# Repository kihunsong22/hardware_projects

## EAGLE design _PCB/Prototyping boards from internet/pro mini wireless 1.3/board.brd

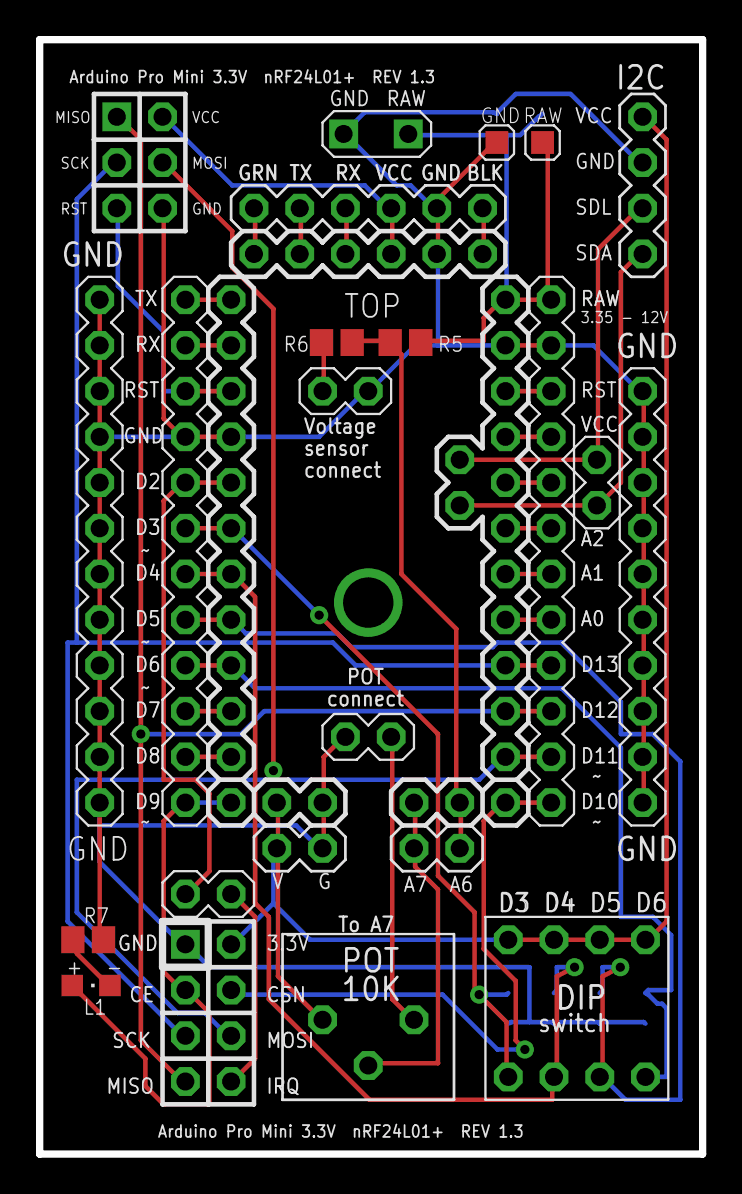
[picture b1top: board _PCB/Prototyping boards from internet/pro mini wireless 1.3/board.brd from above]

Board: 2 copper layers, 36.8 x 61.9 mm, 23 parts (0 on the bottom side), 37 nets.

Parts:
U$1: ARDUINO_PRO_MINI_3.3V
U$2, U$3: 12_PIN_HEADER
U$4: PAD_CONNECT
U$5: 6_PIN_HEADER
U$6: 2_SPACE_2_HEADER
U$7: 18650_HOLDER_FITTED
U$8: 12_PIN_HEADER
U$9: 4-DIP
U$10, U$14, U$15, U$20: 2_PIN_HEADER
U$11: 4_PIN_HEADER
U$12: 10_PIN_HEADER
U$13: POT_10K
U$16, U$17: 1k; 0805_SMD_RESISTOR
U$18: 0805_SMD_LED
U$19: ???R; 0805_SMD_RESISTOR
U$21: NRF24L01; NRFL2401
U$22: SCREWTERMINAL
U$23: SPI

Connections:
BLK: U$1.BLK, U$5.6
GND: U$1.G, U$1.GND_0, U$1.GND_1, U$1.GND_2, U$2.4, U$3.2, U$4.GND_1, U$4.GND_2, U$5.5, U$6.2, U$8.1, U$8.2, U$8.3, U$8.4, U$8.5, U$8.6, U$8.7, U$8.8, U$8.9, U$8.10, U$8.11, U$8.12, U$9.GND_1, U$9.GND_2, U$9.GND_3, U$9.GND_4, U$11.2, U$12.P$1, U$12.P$2, U$12.P$3, U$12.P$4, U$12.P$5, U$12.P$6, U$12.P$7, U$12.P$8, U$12.P$9, U$12.P$10, U$14.2, U$15.1, U$19.2, U$21.GND, U$22.GND, U$23.GND
GRN: U$1.GRN, U$5.1
unnamed: U$1.TX/D0, U$2.1
unnamed: U$1.RX/D1, U$2.2
unnamed: U$1.RST_1, U$2.3, U$23.RESET
unnamed: U$1.RX, U$5.3
unnamed: U$10.1, U$21.IRQ
unnamed: U$1.VCC_0, U$3.4
unnamed: U$1.A5, U$11.3, U$20.1
unnamed: U$1.VCC_1, U$5.4, U$23.VCC
unnamed: U$15.2, U$16.1
unnamed: U$13.CCW, U$14.1
unnamed: U$18.C, U$19.1
unnamed: U$1.D10, U$3.12, U$21.CSN
unnamed: U$1.D11, U$3.11, U$21.MOSI, U$23.MOSI
unnamed: U$1.D3, U$2.6, U$9.D3, U$9.OFF_1
unnamed: U$1.RST_0, U$3.3
unnamed: U$1.A3, U$3.5
unnamed: U$1.A2, U$3.6
unnamed: U$1.A1, U$3.7
unnamed: U$1.A0, U$3.8
unnamed: U$1.A4, U$11.4, U$20.2
unnamed: U$1.A6, U$6.4, U$16.2, U$17.1
unnamed: U$1.D9, U$2.12, U$18.A, U$21.CE
unnamed: U$1.D2, U$2.5, U$10.2
unnamed: U$1.A7, U$6.3, U$13.WIPER
unnamed: U$1.RAW, U$3.1, U$4.RAW_1, U$4.RAW_2, U$17.2, U$22.RAW_3
unnamed: U$1.D12, U$3.10, U$21.MISO, U$23.MISO
unnamed: U$1.D5, U$2.8, U$9.D5, U$9.OFF_3
unnamed: U$1.D4, U$2.7, U$9.D4, U$9.OFF_2
unnamed: U$1.D7, U$2.10
unnamed: U$1.D8, U$2.11
unnamed: U$1.D6, U$2.9, U$9.D6, U$9.OFF_4
unnamed: U$1.D13, U$3.9, U$21.SCK, U$23.SCK
TX: U$1.TX, U$5.2
VCC: U$1.V, U$6.1, U$9.VCC_1, U$9.VCC_2, U$9.VCC_3, U$9.VCC_4, U$11.1, U$13.CW, U$21.3.3V

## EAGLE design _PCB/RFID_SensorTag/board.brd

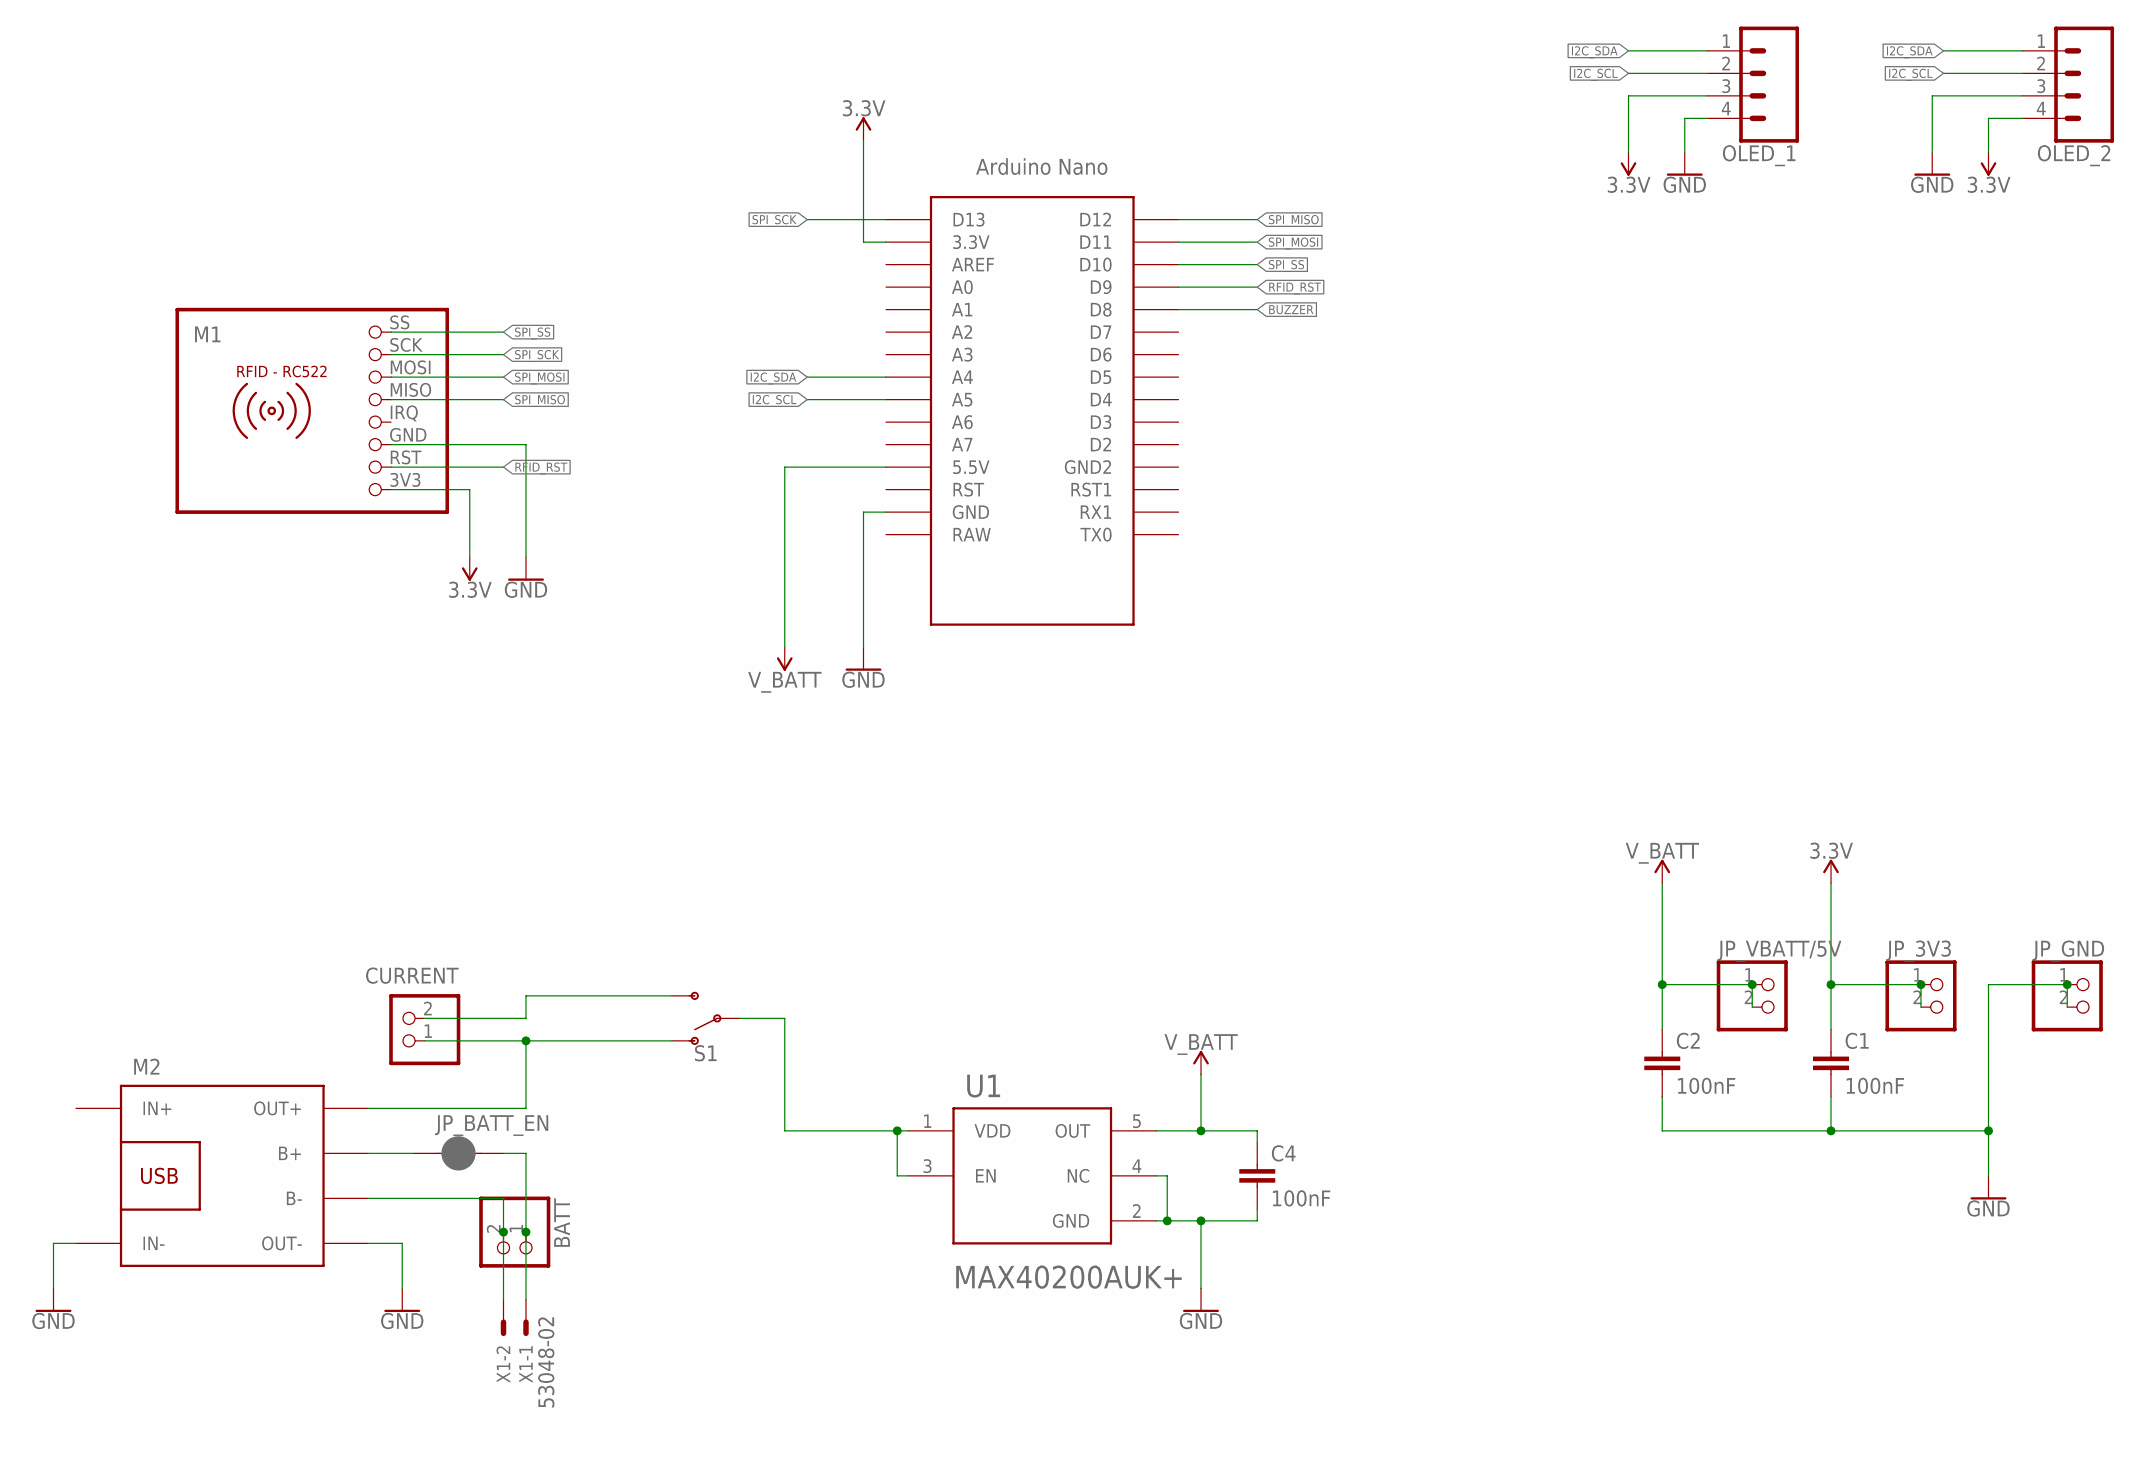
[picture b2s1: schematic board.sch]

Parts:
BATT: PINHD-1X2; 1X02
C1, C2, C4: 100nF; C0805
CURRENT: PINHD-1X2; 1X02
JP_3V3: PINHD-1X2; 1X02
JP_BATT_EN: JUMPER-SMT_2_NC_PASTE_SILK; SMT-JUMPER_2_NC_PASTE_SILK
JP_GND: PINHD-1X2; 1X02
JP_VBATT/5V: PINHD-1X2; 1X02
M1: RFID-RC522
M2: BATTERY-CHARGER-LI-PROT
OLED_1, OLED_2: CONN_04; 1X04
S1: SWITCH-SPDT-PTH-11.6X4.0MM; SWITCH_SPDT_PTH_11.6X4.0MM
U1: MAXIM_ELECTRONICS_MAX40200AUK+MAXIM_ELECTRONICS_M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; MAXIM_ELECTRONICS_MAX40200AUK+_0
U$1: NANO_ICSP-REMOVED
X1: 53048-02

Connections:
3.3V: C1.1, JP_3V3.1, JP_3V3.2, M1.3V3 (1), OLED_1.3, OLED_2.4, U$1.3.3V
BATT_VOUT: S1.2, U1.1 (VDD), U1.3 (EN)
BUZZER: U$1.D8
GND: C1.2, C2.2, C4.2, JP_GND.1, JP_GND.2, M1.GND (3), M2.IN-, M2.OUT-, OLED_1.4, OLED_2.3, U1.2 (GND), U1.4 (NC), U$1.GND
I2C_SCL: OLED_1.2, OLED_2.2, U$1.A5
I2C_SDA: OLED_1.1, OLED_2.1, U$1.A4
unnamed: CURRENT.1, M2.OUT+, S1.1 (O)
unnamed: BATT.1, JP_BATT_EN.2, X1.1
unnamed: CURRENT.2, S1.3 (S)
unnamed: BATT.2, M2.B-, X1.2
unnamed: JP_BATT_EN.1, M2.B+
RFID_RST: M1.RST (2), U$1.D9
SPI_MISO: M1.MISO (5), U$1.D12
SPI_MOSI: M1.MOSI (6), U$1.D11
SPI_SCK: M1.SCK (7), U$1.D13
SPI_SS: M1.SS (8), U$1.D10
V_BATT: C2.1, C4.1, JP_VBATT/5V.1, JP_VBATT/5V.2, U1.5 (OUT), U$1.5V (5.5V)

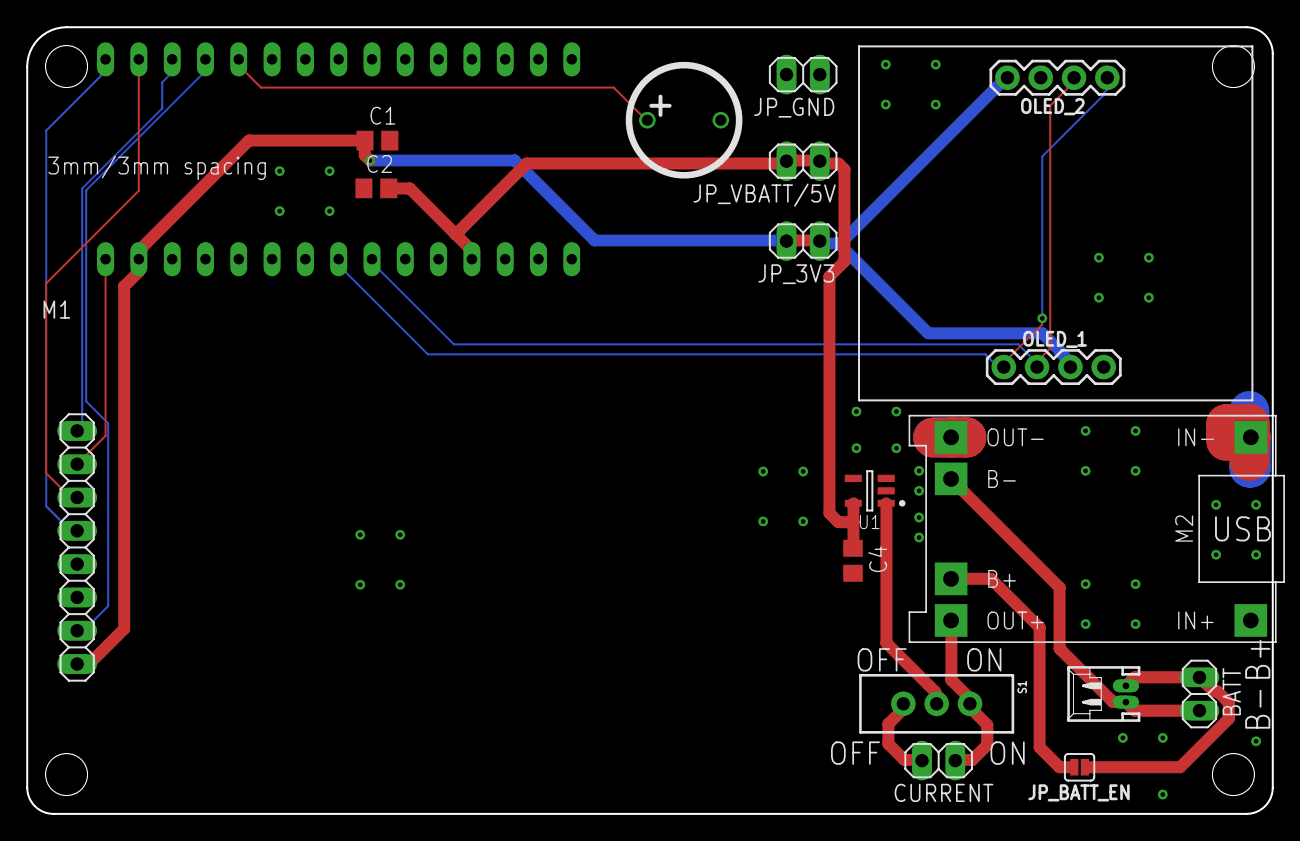
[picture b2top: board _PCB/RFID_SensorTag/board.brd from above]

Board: 2 copper layers, 95.0 x 60.0 mm, 17 parts (0 on the bottom side), 16 nets.

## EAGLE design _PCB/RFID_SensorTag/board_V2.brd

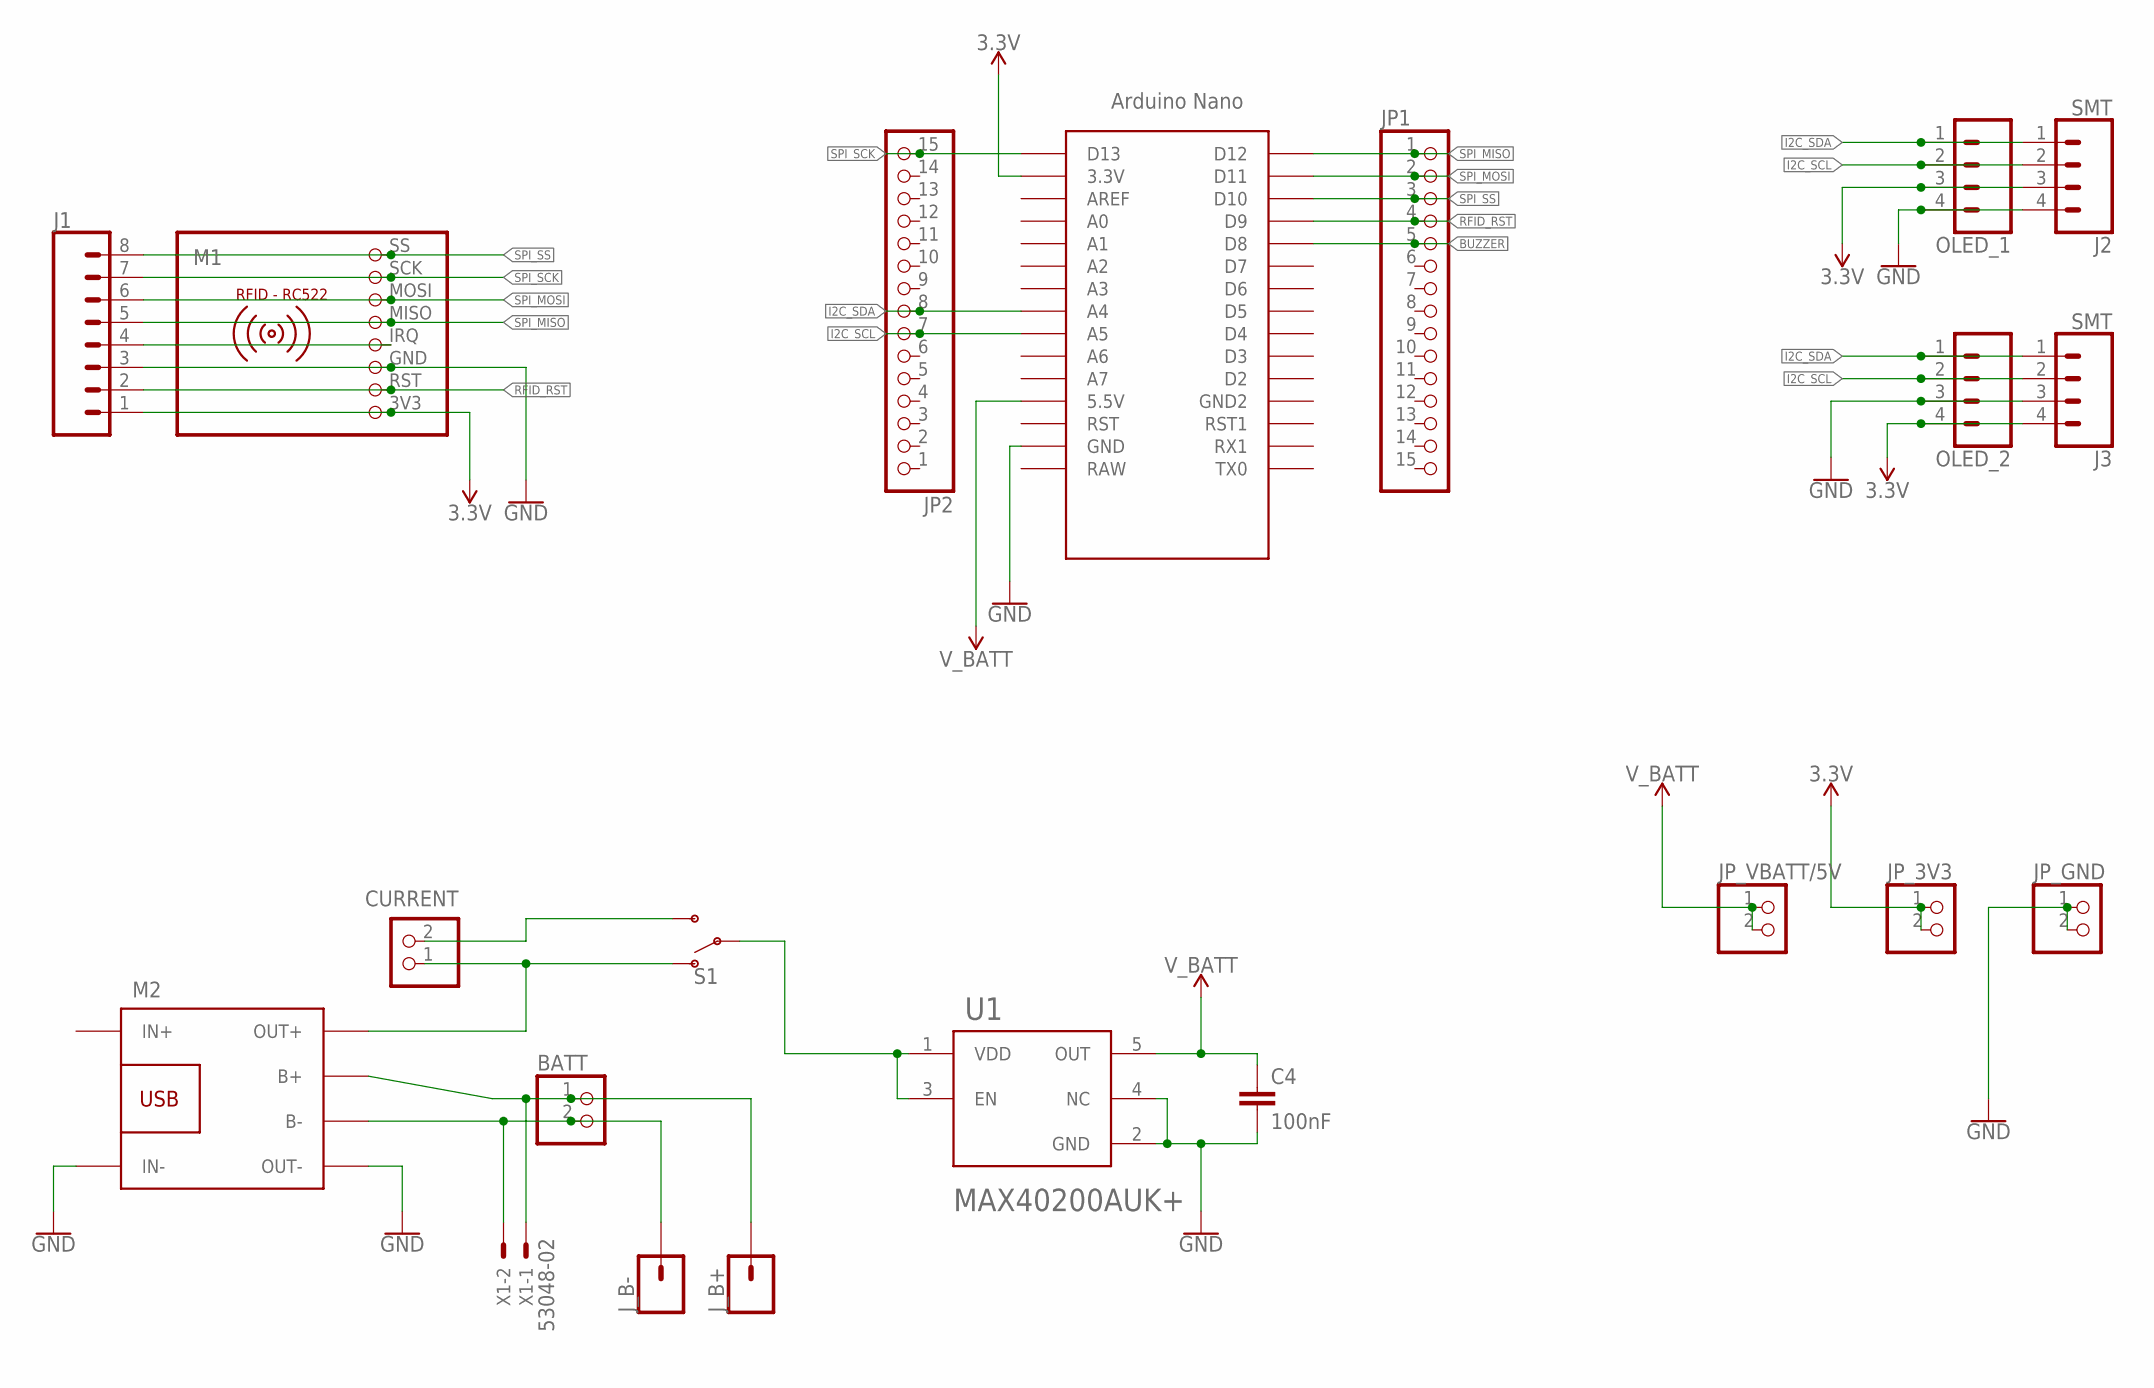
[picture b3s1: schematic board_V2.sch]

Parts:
BATT: PINHD-1X2; 1X02
C4: 100nF; C0805
CURRENT: PINHD-1X2; 1X02
J1: CONN_08SMD-COMBO-FEMALE; 1X08_SMD_COMBINED
J2, J3: SMT; 1X04_SMD_VERTICAL_COMBO
JP1, JP2: PINHD-1X151X15_SMT; 1X15_SMT
JP_3V3: PINHD-1X2; 1X02
JP_GND: PINHD-1X2; 1X02
JP_VBATT/5V: PINHD-1X2; 1X02
J_B+: CONN_01OFFSET; 1X01_OFFSET
J_B-: CONN_01OFFSET; 1X01_OFFSET
M1: RFID-RC522
M2: BATTERY-CHARGER-LI-PROT
OLED_1, OLED_2: CONN_04; 1X04
S1: SWITCH-SPDT-PTH-11.6X4.0MM; SWITCH_SPDT_PTH_11.6X4.0MM
U1: MAXIM_ELECTRONICS_MAX40200AUK+MAXIM_ELECTRONICS_M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; MAXIM_ELECTRONICS_MAX40200AUK+_0
U$1: NANO_ICSP-REMOVED
X1: 53048-02

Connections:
3.3V: J1.1, J2.3, J3.4, JP_3V3.1, JP_3V3.2, M1.3V3 (1), OLED_1.3, OLED_2.4, U$1.3.3V
BATT_VOUT: S1.2, U1.1 (VDD), U1.3 (EN)
BUZZER: JP1.5, U$1.D8
GND: C4.2, J1.3, J2.4, J3.3, JP_GND.1, JP_GND.2, M1.GND (3), M2.IN-, M2.OUT-, OLED_1.4, OLED_2.3, U1.2 (GND), U1.4 (NC), U$1.GND
I2C_SCL: J2.2, J3.2, JP2.7, OLED_1.2, OLED_2.2, U$1.A5
I2C_SDA: J2.1, J3.1, JP2.8, OLED_1.1, OLED_2.1, U$1.A4
unnamed: BATT.1, J_B+.1, M2.B+, X1.1
unnamed: CURRENT.1, M2.OUT+, S1.1 (O)
unnamed: J1.4, M1.IRQ (4)
unnamed: CURRENT.2, S1.3 (S)
unnamed: BATT.2, J_B-.1, M2.B-, X1.2
RFID_RST: J1.2, JP1.4, M1.RST (2), U$1.D9
SPI_MISO: J1.5, JP1.1, M1.MISO (5), U$1.D12
SPI_MOSI: J1.6, JP1.2, M1.MOSI (6), U$1.D11
SPI_SCK: J1.7, JP2.15, M1.SCK (7), U$1.D13
SPI_SS: J1.8, JP1.3, M1.SS (8), U$1.D10
V_BATT: C4.1, JP_VBATT/5V.1, JP_VBATT/5V.2, U1.5 (OUT), U$1.5V (5.5V)

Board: 2 copper layers, 21 parts (0 on the bottom side), 17 nets, no tracks yet.

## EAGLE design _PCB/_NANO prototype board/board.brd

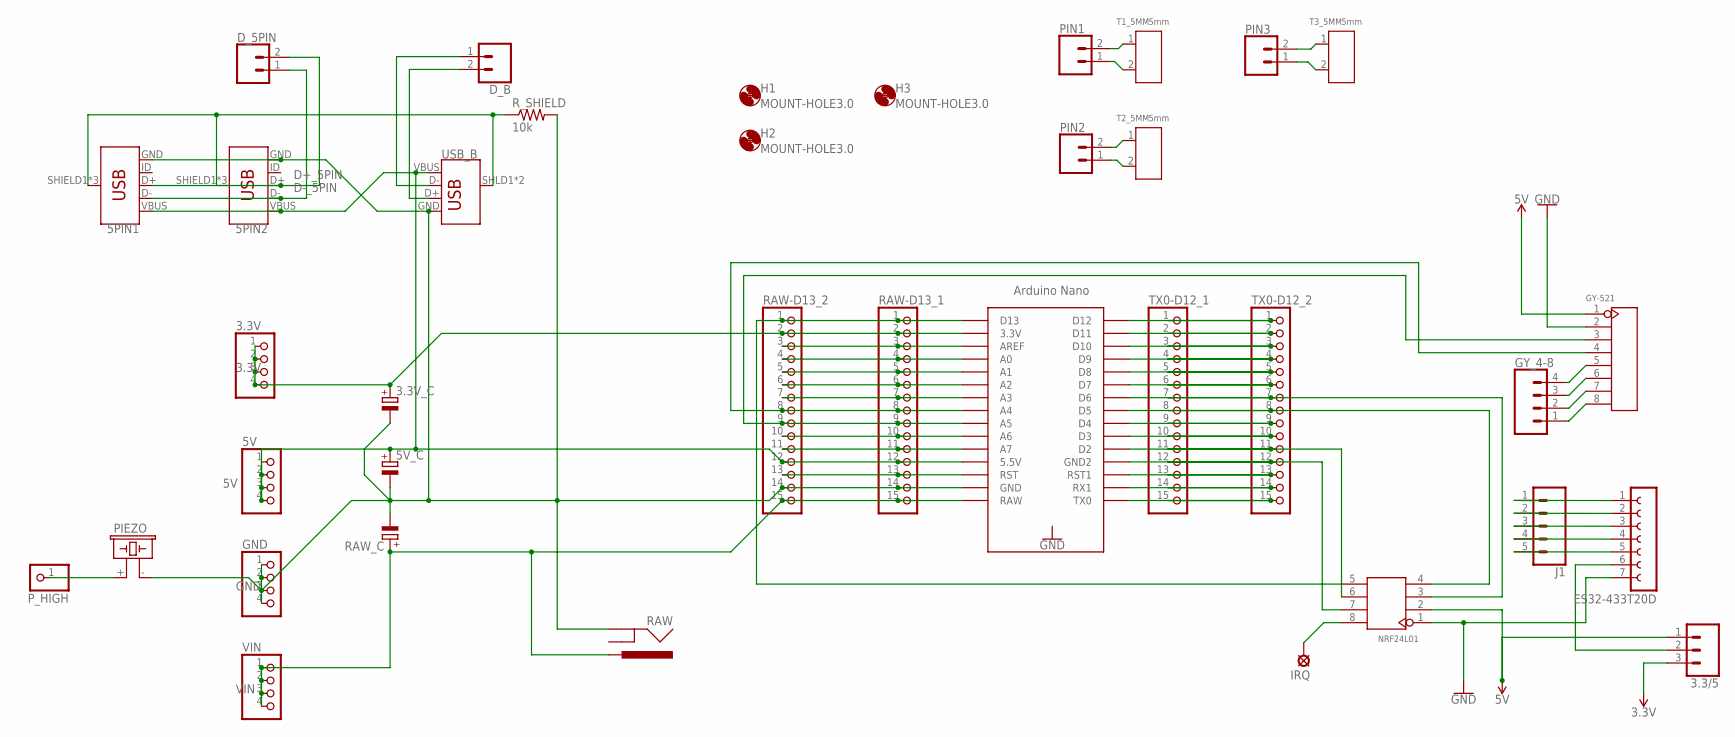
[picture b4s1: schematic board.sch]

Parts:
3.3/5: CONN_03LOCK; 1X03_LOCK
3.3V, 5V: PINHD-1X4; 1X04
3.3V_C: CPOL-EUE2.5-5; E2,5-5
5PIN1, 5PIN2: USB_MICRO-B_FEMALE-SMT; USB-B-MICRO-SMD
5V_C: CPOL-EUE3.5-8; E3,5-8
D_5PIN: CONN_02LOCK; 1X02_LOCK
D_B: CONN_02LOCK; 1X02_LOCK
ES32-433T20D: FE07-1; FE07
GND: PINHD-1X4; 1X04
GY-521: DIP-BLACK-FEMALE-HEADER-VERT(8P-2.54); H8-2.54
GY_4-8: CONN_04; 1X04
H1, H2, H3: MOUNT-HOLE3.0; 3,0
IRQ: LSP10
J1: CONN_05; 1X05
NANO: NANO
NRF24L01: DIP-BLACK-FEMALE-HEADER(2X4P-2.54); H2X4-2.54
PIEZO: F/CM12P
PIN1, PIN2, PIN3: CONN_02LOCK; 1X02_LOCK
P_HIGH: PINHD-1X1/OCT; 1X01/OCT
RAW: POWER_JACKSLT; POWER_JACK_SLOT
RAW-D13_1, RAW-D13_2: PINHD-1X15; 1X15
RAW_C: CPOL-EUE3.5-8; E3,5-8
R_SHIELD: 10k; 0204/5
T1_5MM, T2_5MM, T3_5MM: 5mm; H2-5.0-10.5X8.0MM
TX0-D12_1, TX0-D12_2: PINHD-1X15; 1X15
USB_B: USB_B_PTH; USB-B-PTH
VIN: PINHD-1X4; 1X04

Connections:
3.3V: 3.3/5.3, 3.3V.1, 3.3V.2, 3.3V.3, 3.3V.4, 3.3V_C.+, NANO.3.3V, RAW-D13_1.2, RAW-D13_2.2
5V: 3.3/5.1, 5PIN1.VBUS, 5PIN2.VBUS, 5V.1, 5V.2, 5V.3, 5V.4, 5V_C.+, GY-521.1, NANO.5V (5.5V), NRF24L01.2, RAW-D13_1.12, RAW-D13_2.12, USB_B.VBUS
A5: GY-521.3, NANO.A5, RAW-D13_1.9, RAW-D13_2.9
A6: NANO.A6, RAW-D13_1.10, RAW-D13_2.10
A7: NANO.A7, RAW-D13_1.11, RAW-D13_2.11
CE_NRF: NANO.D6, NRF24L01.3, TX0-D12_1.7, TX0-D12_2.7
CSN_NRF: NANO.D5, NRF24L01.4, TX0-D12_1.8, TX0-D12_2.8
D+_5PIN: 5PIN1.D+, 5PIN2.D+, D_5PIN.2
D-_5PIN: 5PIN1.D-, 5PIN2.D-, D_5PIN.1
GND: 3.3V_C.-, 5PIN1.GND, 5PIN2.GND, 5V_C.-, ES32-433T20D.7, GND.1, GND.2, GND.3, GND.4, GY-521.2, NANO.GND, NANO.ICSP6, NRF24L01.1, PIEZO.- (2), RAW.GND@2 (GND), RAW-D13_1.14, RAW-D13_2.14, RAW_C.-, R_SHIELD.2, USB_B.GND
MISO_NRF: NANO.GND1 (GND2), NRF24L01.7, TX0-D12_1.12, TX0-D12_2.12
MOSI_NRF: NANO.D2, NRF24L01.6, TX0-D12_1.11, TX0-D12_2.11
unnamed: IRQ.MP, NRF24L01.8
unnamed: GY-521.5, GY_4-8.4
unnamed: NANO.AREF, RAW-D13_1.3, RAW-D13_2.3
unnamed: NANO.A0, RAW-D13_1.4, RAW-D13_2.4
unnamed: NANO.A1, RAW-D13_1.5, RAW-D13_2.5
unnamed: NANO.A2, RAW-D13_1.6, RAW-D13_2.6
unnamed: NANO.A3, RAW-D13_1.7, RAW-D13_2.7
unnamed: GY-521.6, GY_4-8.3
unnamed: GY-521.7, GY_4-8.2
unnamed: GY-521.8, GY_4-8.1
unnamed: 3.3/5.2, ES32-433T20D.6
unnamed: ES32-433T20D.1, J1.1
unnamed: ES32-433T20D.2, J1.2
unnamed: ES32-433T20D.3, J1.3
unnamed: ES32-433T20D.4, J1.4
unnamed: NANO.D12, TX0-D12_1.1, TX0-D12_2.1
unnamed: NANO.D11, TX0-D12_1.2, TX0-D12_2.2
unnamed: NANO.D10, TX0-D12_1.3, TX0-D12_2.3
unnamed: NANO.D9, TX0-D12_1.4, TX0-D12_2.4
unnamed: NANO.D8, TX0-D12_1.5, TX0-D12_2.5
unnamed: NANO.D7, TX0-D12_1.6, TX0-D12_2.6
unnamed: ES32-433T20D.5, J1.5
unnamed: PIN1.2, T1_5MM.1
unnamed: NANO.D4, TX0-D12_1.9, TX0-D12_2.9
unnamed: NANO.D3, TX0-D12_1.10, TX0-D12_2.10
unnamed: PIN1.1, T1_5MM.2
unnamed: PIN2.2, T2_5MM.1
unnamed: NANO.RST1, TX0-D12_1.13, TX0-D12_2.13
unnamed: NANO.RX1, TX0-D12_1.14, TX0-D12_2.14
unnamed: NANO.TX0, TX0-D12_1.15, TX0-D12_2.15
unnamed: PIN2.1, T2_5MM.2
unnamed: PIN3.2, T3_5MM.1
unnamed: PIN3.1, T3_5MM.2
unnamed: PIEZO.+ (1), P_HIGH.1
unnamed: D_B.1, USB_B.D-
unnamed: D_B.2, USB_B.D+
RST: NANO.RST, RAW-D13_1.13, RAW-D13_2.13
SCK_NRF: NANO.D13, NRF24L01.5, RAW-D13_1.1, RAW-D13_2.1
SDA_GY521: GY-521.4, NANO.A4, RAW-D13_1.8, RAW-D13_2.8
SHIELD_IN: 5PIN1.SHIELD1 (SHIELD), 5PIN1.SHIELD2 (SHIELD), 5PIN1.SHIELD3 (SHIELD), 5PIN2.SHIELD1 (SHIELD), 5PIN2.SHIELD2 (SHIELD), 5PIN2.SHIELD3 (SHIELD), R_SHIELD.1, USB_B.SHLD1 (SHIELD), USB_B.SHLD2 (SHIELD)
VIN: NANO.RAW, RAW.PWR, RAW-D13_1.15, RAW-D13_2.15, RAW_C.+, VIN.1, VIN.2, VIN.3, VIN.4

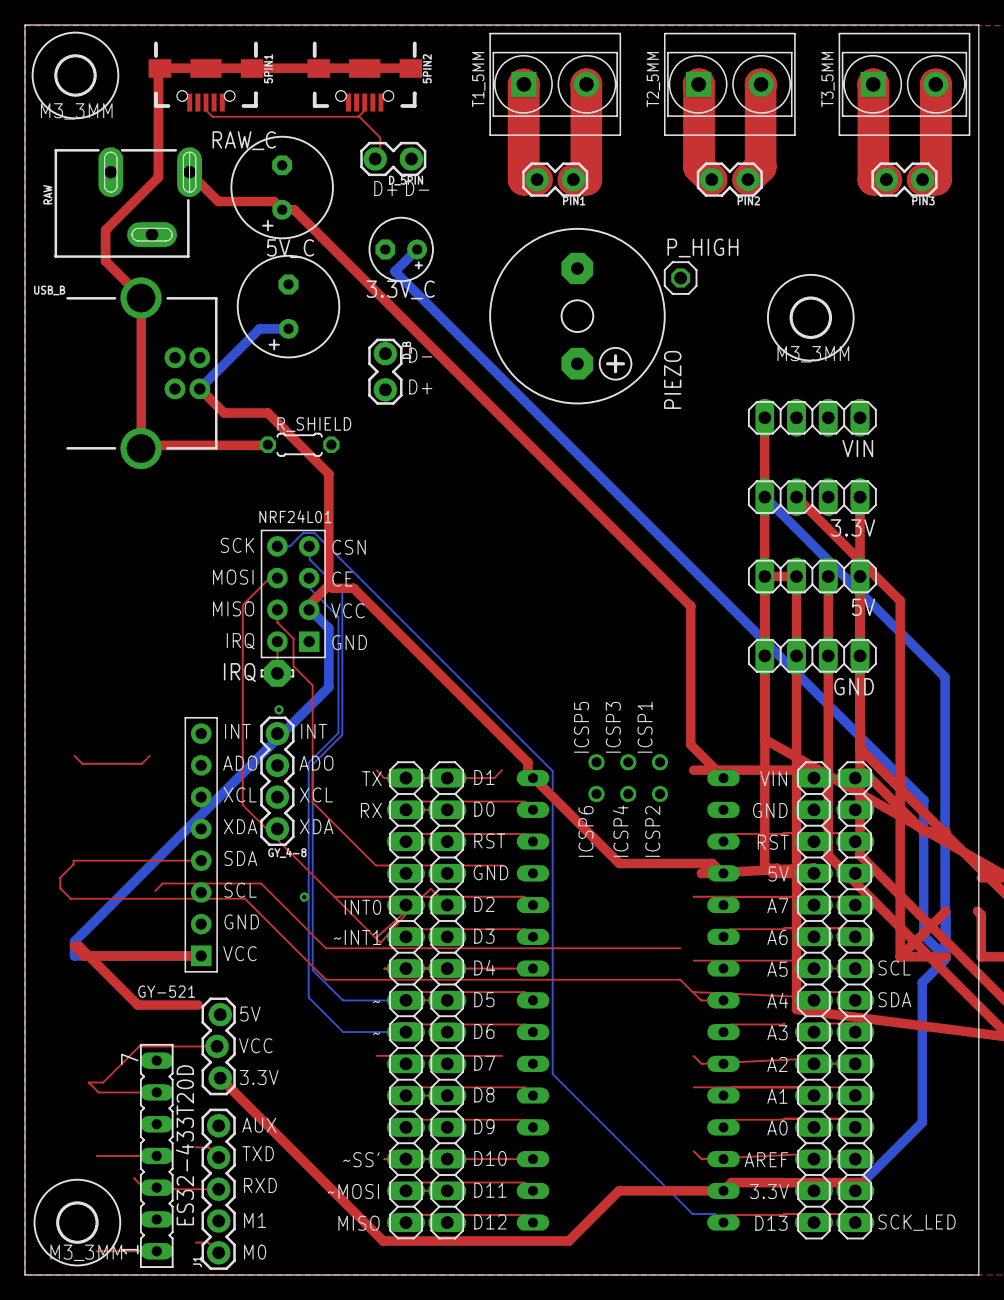
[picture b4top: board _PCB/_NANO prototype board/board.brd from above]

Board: 2 copper layers, 76.3 x 100.0 mm, 37 parts (0 on the bottom side), 53 nets.

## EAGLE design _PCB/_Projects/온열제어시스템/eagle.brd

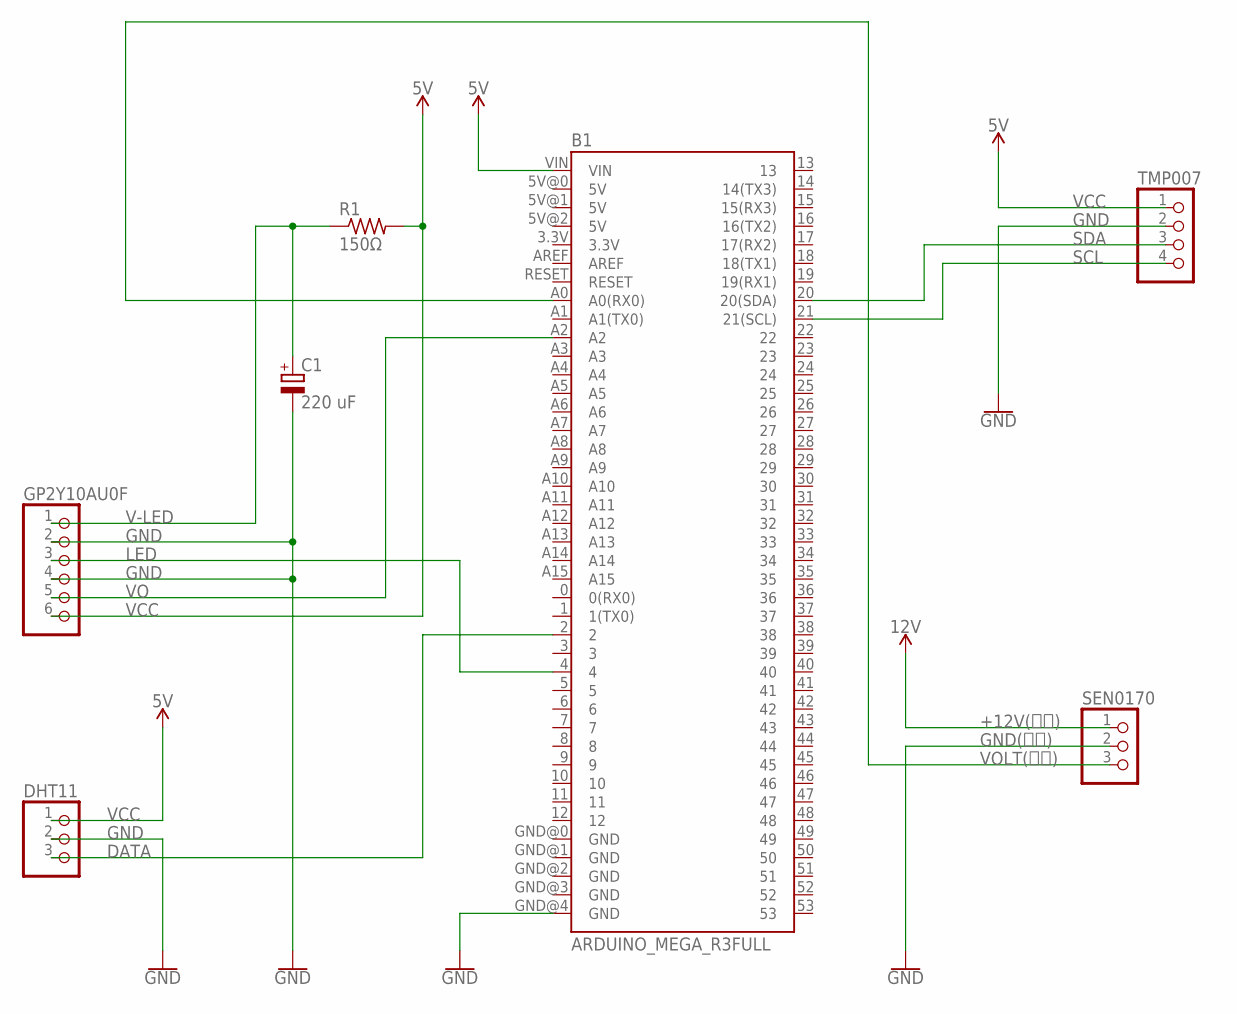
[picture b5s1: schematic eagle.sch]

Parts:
B1: ARDUINO_MEGA_R3FULL; ARDUINO_MEGA
C1: 220 uF; E2,5-5
DHT11: PINHD-1X3; 1X03
GP2Y10AU0F: PINHD-1X6; 1X06
R1: 150Ω; R1206
SEN0170: PINHD-1X3; 1X03
TMP007: PINHD-1X4; 1X04

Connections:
+12V(적색): SEN0170.1
DATA: B1.2, DHT11.3
GND: B1.GND@4 (GND), C1.-, DHT11.2, GP2Y10AU0F.2, GP2Y10AU0F.4, TMP007.2
GND(흑색): SEN0170.2
LED: B1.4, GP2Y10AU0F.3
SCL: B1.21 (21(SCL)), TMP007.4
SDA: B1.20 (20(SDA)), TMP007.3
V-LED: C1.+, GP2Y10AU0F.1, R1.1
VCC: B1.VIN, DHT11.1, GP2Y10AU0F.6, R1.2, TMP007.1
VO: B1.A2, GP2Y10AU0F.5
VOLT(황색): B1.A0 (A0(RX0)), SEN0170.3

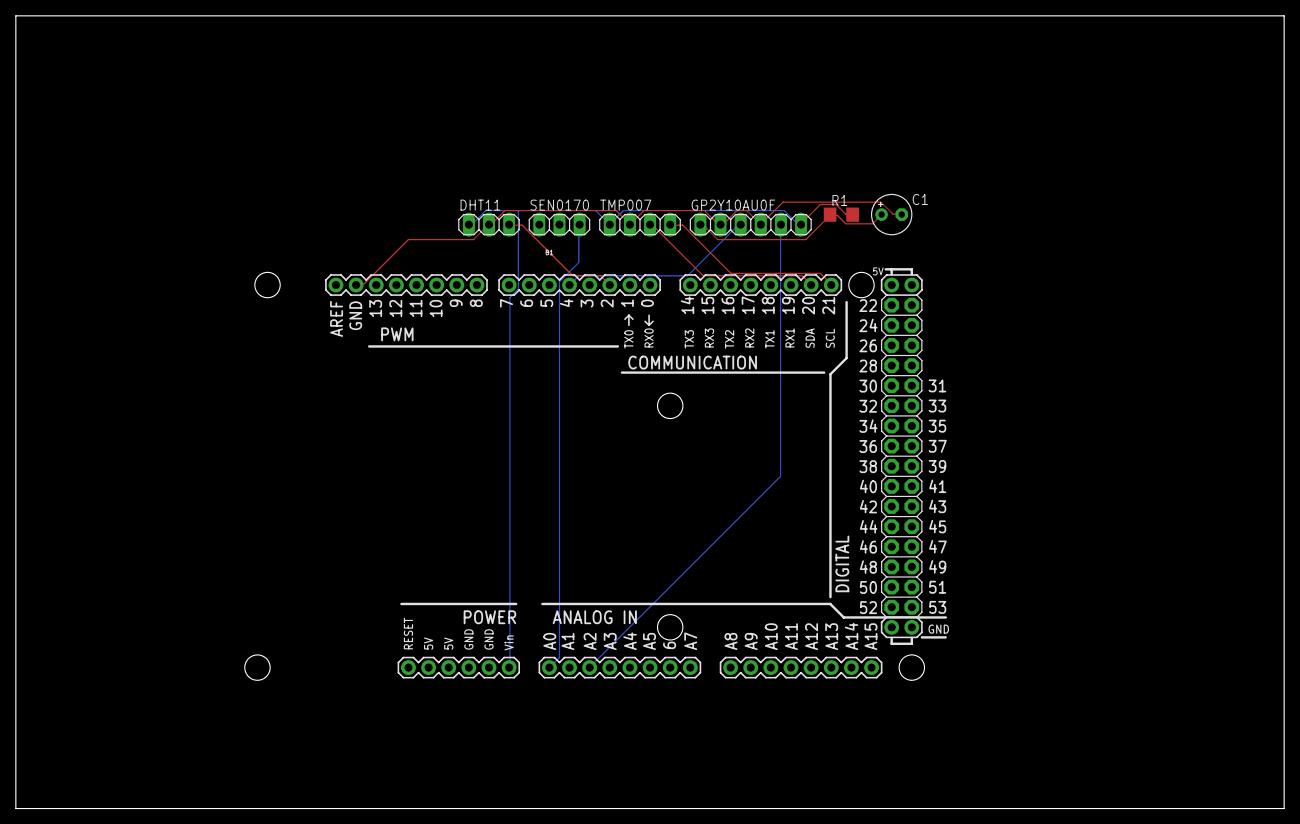
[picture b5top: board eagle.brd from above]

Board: 2 copper layers, 160.0 x 100.0 mm, 7 parts (0 on the bottom side), 9 nets.

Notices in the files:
parts and their libraries:
SparkFun-Aesthetics: Licensing: Creative Commons ShareAlike 4.0 International - https://creativecommons.org/licenses/by-sa/4.0
diy-modules: Released under the Creative Commons Attribution 4.0 International License: http://creativecommons.org/licenses/by/4.0
